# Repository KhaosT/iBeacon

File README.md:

iBeacon
=======
My own implementation of iBeacon.

/Eagle contains different version of hardware design. All designs based on TI CC2541.

/iOS contains a configurator for iBeacon used to setup UUID, Major and Minor when doing field work.

/Firmware contains firmware for CC2541.

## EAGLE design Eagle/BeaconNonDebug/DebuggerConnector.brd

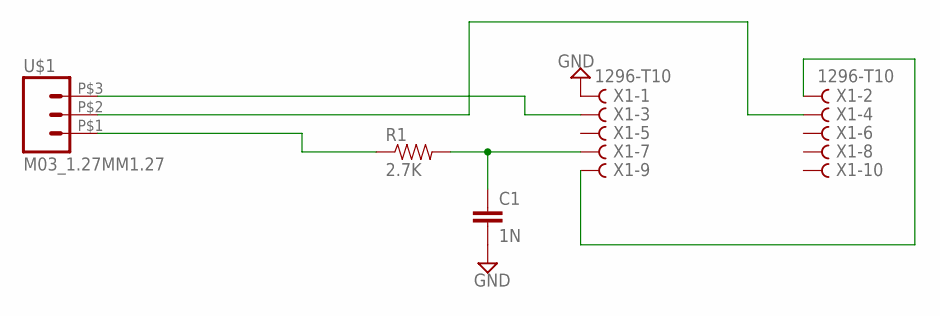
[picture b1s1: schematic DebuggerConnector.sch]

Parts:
C1: 1N; 0402-CAP
R1: 2.7K; 0402-RES
U$1: M03_1.27MM1.27; 1X3_1.27MM
X1: 1296-T10; 1296-10

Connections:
GND: C1.2, X1.1
unnamed: U$1.P$3 (3), X1.3
unnamed: U$1.P$2 (2), X1.4
unnamed: R1.1, U$1.P$1 (1)
unnamed: C1.1, R1.2, X1.7
unnamed: X1.2, X1.9

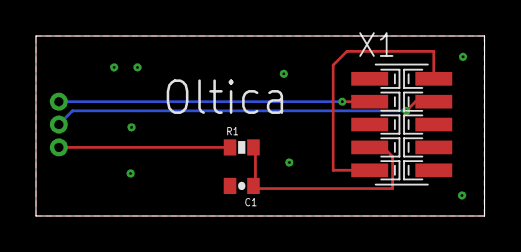
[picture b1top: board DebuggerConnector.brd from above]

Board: 2 copper layers, 24.9 x 10.0 mm, 4 parts (0 on the bottom side), 6 nets.

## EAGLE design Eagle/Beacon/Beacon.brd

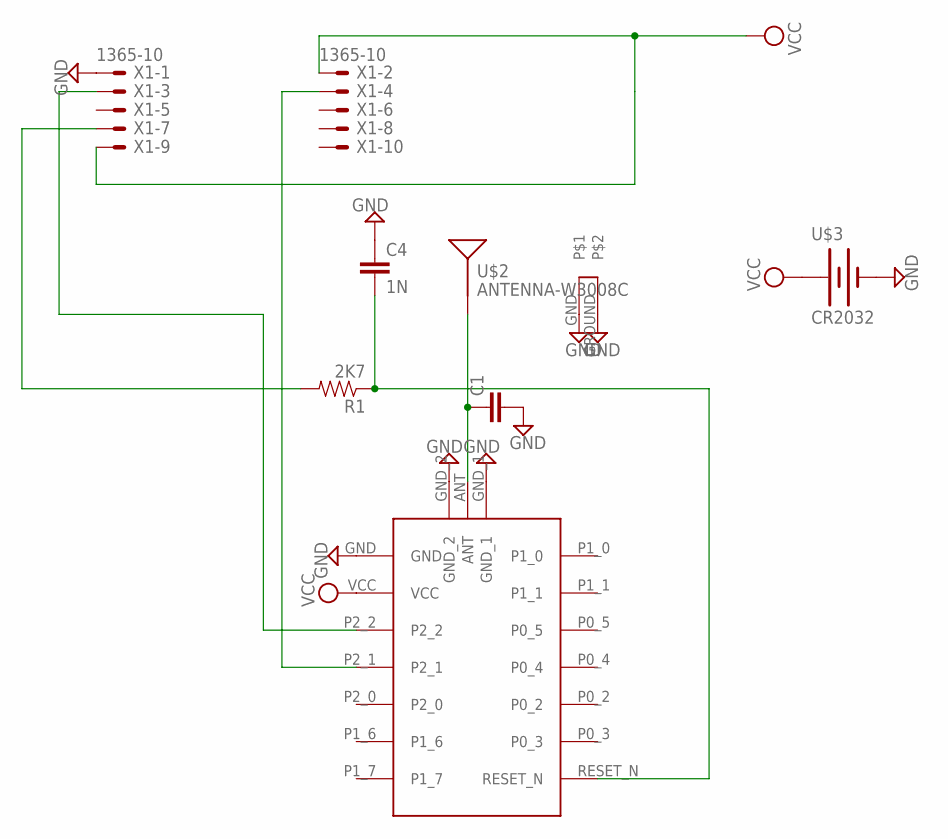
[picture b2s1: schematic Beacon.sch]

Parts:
C1: CAP0402-CAP; 0402-CAP
C4: 1N; 0402-CAP
R1: 2K7; 0402-RES
U$1: BLE4
U$2: ANTENNA-W3008C
U$3: CR2032; BATTCON_2032
X1: 1365-10

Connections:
GND: C1.2, C4.1, U$1.GND, U$1.GND_1, U$1.GND_2, U$2.GND, U$2.GROUND, U$3.PWR@2 (-), X1.1
unnamed: C1.1, U$1.ANT, U$2.FEED (SIGNAL)
unnamed: U$1.P2_2, X1.3
unnamed: C4.2, R1.1, U$1.RESET_N
unnamed: U$1.P2_1, X1.4
unnamed: R1.2, X1.7
VCC: U$1.VCC, U$3.PWR@1 (+), X1.2, X1.9

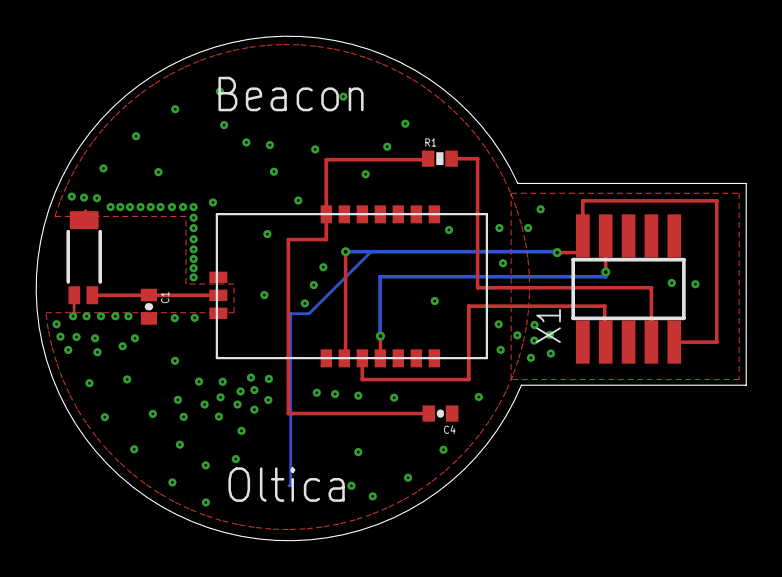
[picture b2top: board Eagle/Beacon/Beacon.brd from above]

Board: 2 copper layers, 39.4 x 28.0 mm, 7 parts (1 on the bottom side), 7 nets.

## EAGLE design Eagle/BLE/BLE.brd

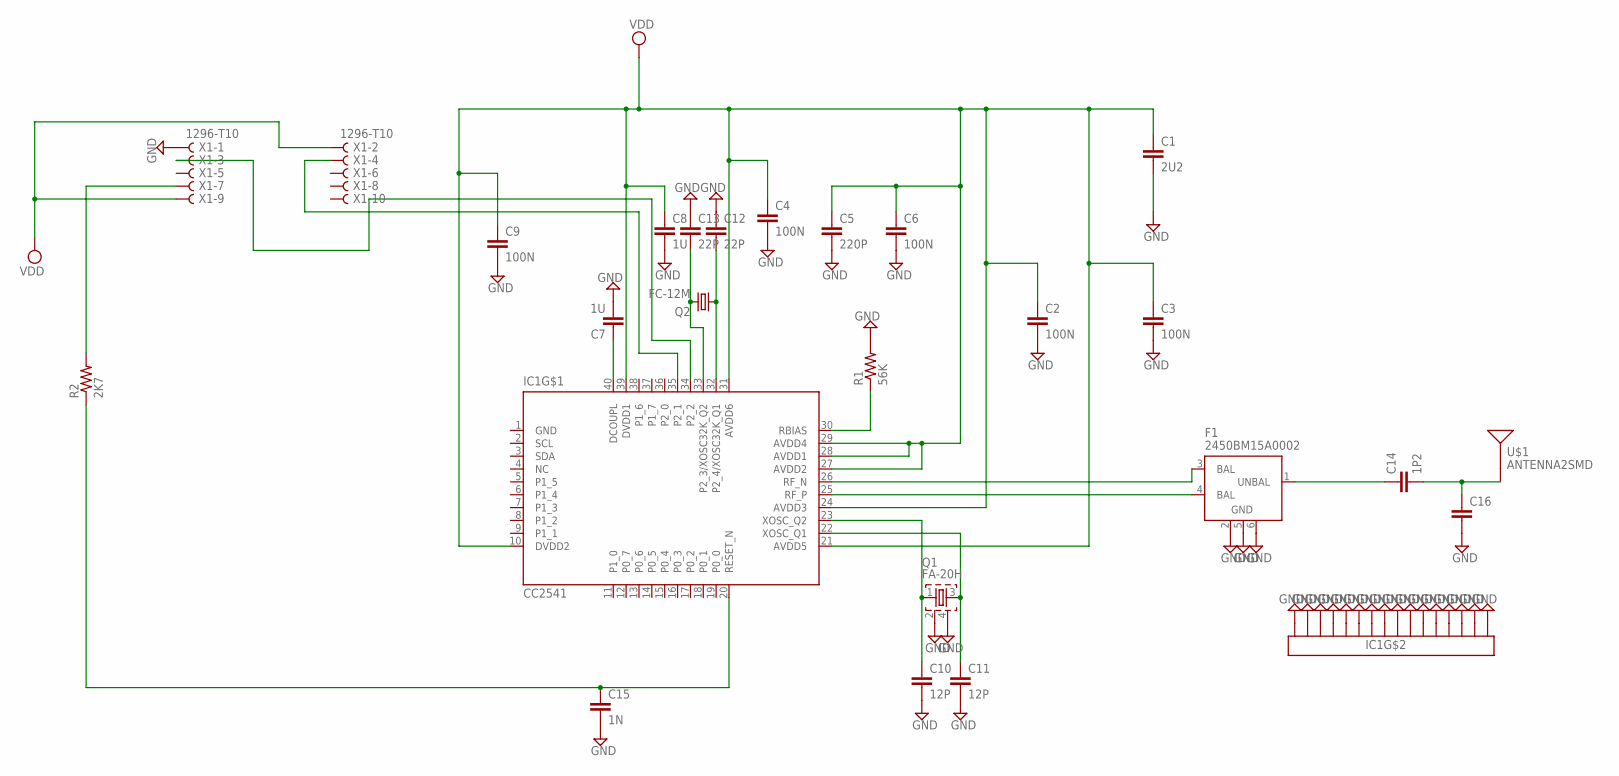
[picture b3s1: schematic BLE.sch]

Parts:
C1: 2U2; 0402-CAP
C2, C3, C4, C6, C9: 100N; 0402-CAP
C5: 220P; 0402-CAP
C7, C8: 1U; 0402-CAP
C10, C11: 12P; 0402-CAP
C12, C13: 22P; 0402-CAP
C14: 1P2; 0402-CAP
C15: 1N; 0402-CAP
C16: CAP0402-CAP; 0402-CAP
F1: 2450BM15A0002
IC1: CC2541; QFN40-6X6
Q1: FA-20H
Q2: FC-12M
R1: 56K; 0402-RES
R2: 2K7; 0402-RES
U$1: ANTENNA2SMD; ANTENNA-CHIP2
X1: 1296-T10; 1296-10

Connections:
GND: C1.2, C2.2, C3.2, C4.2, C5.2, C6.2, C7.2, C8.2, C9.2, C10.2, C11.2, C12.1, C13.1, C15.2, C16.2, F1.2 (GND), F1.5 (GND), F1.6 (GND), IC1.1 (GND), IC1.EXP@1 (EXP16), IC1.EXP@2 (EXP16), IC1.EXP@3 (EXP16), IC1.EXP@4 (EXP16), IC1.EXP@5 (EXP16), IC1.EXP@6 (EXP16), IC1.EXP@7 (EXP16), IC1.EXP@8 (EXP16), IC1.EXP@9 (EXP16), IC1.EXP@10 (EXP16), IC1.EXP@11 (EXP16), IC1.EXP@12 (EXP16), IC1.EXP@13 (EXP16), IC1.EXP@14 (EXP16), IC1.EXP@15 (EXP16), IC1.EXP@16 (EXP16), Q1.2, Q1.4, R1.2, X1.1
unnamed: IC1.30 (RBIAS), R1.1
unnamed: C7.1, IC1.40 (DCOUPL)
unnamed: C11.1, IC1.22 (XOSC_Q1), Q1.3
unnamed: C10.1, IC1.23 (XOSC_Q2), Q1.1
unnamed: C12.2, IC1.32 (P2_4/XOSC32K_Q1), Q2.1
unnamed: C13.2, IC1.33 (P2_3/XOSC32K_Q2), Q2.2
unnamed: F1.3 (BAL), IC1.26 (RF_N)
unnamed: F1.4 (BAL), IC1.25 (RF_P)
unnamed: C14.1, F1.1 (UNBAL)
unnamed: C14.2, C16.1, U$1.FEED
unnamed: C15.1, IC1.20 (RESET_N), R2.1
unnamed: R2.2, X1.7
unnamed: IC1.34 (P2_2), X1.3
unnamed: IC1.35 (P2_1), X1.4
NC: IC1.4 (NC)
VDD: C1.1, C2.1, C3.1, C4.1, C5.1, C6.1, C8.1, C9.1, IC1.10 (DVDD2), IC1.21 (AVDD5), IC1.24 (AVDD3), IC1.27 (AVDD2), IC1.28 (AVDD1), IC1.29 (AVDD4), IC1.31 (AVDD6), IC1.39 (DVDD1), X1.2, X1.9

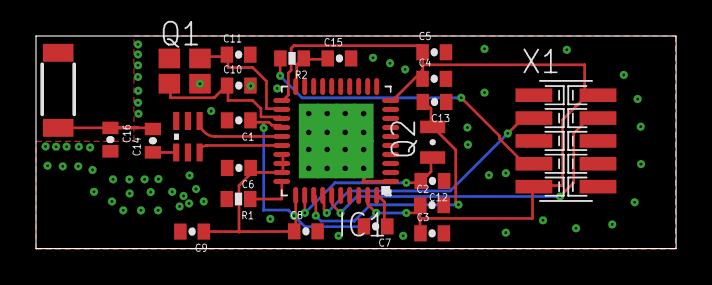
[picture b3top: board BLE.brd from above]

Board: 2 copper layers, 35.6 x 11.8 mm, 24 parts (0 on the bottom side), 16 nets.

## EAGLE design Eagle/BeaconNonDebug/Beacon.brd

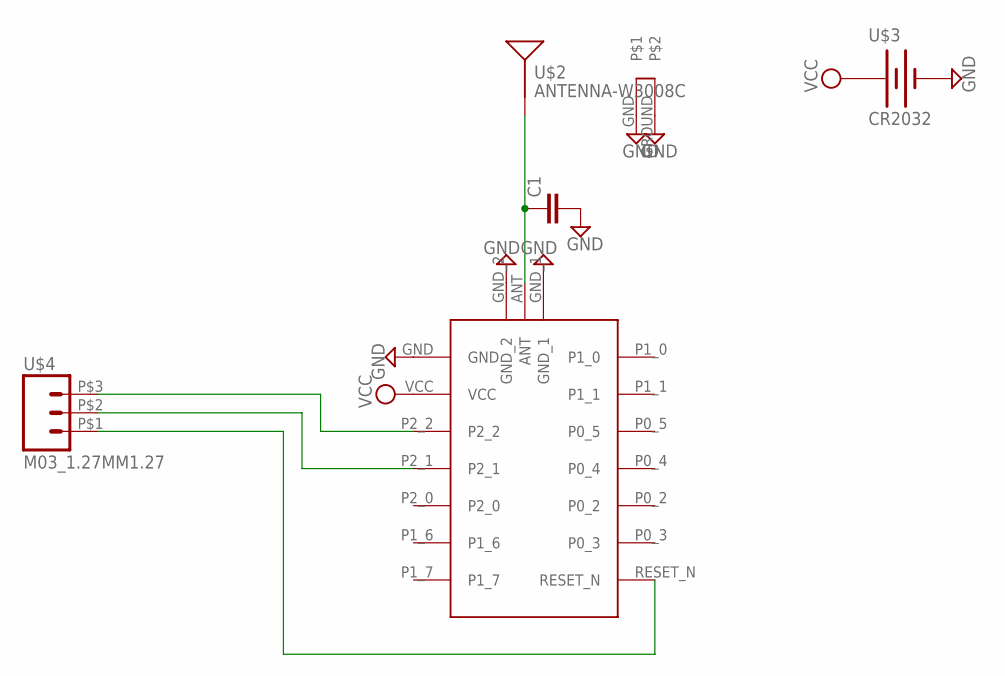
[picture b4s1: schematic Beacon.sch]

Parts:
C1: CAP0402-CAP; 0402-CAP
U$1: BLE4
U$2: ANTENNA-W3008C
U$3: CR2032; BATTCON_2032
U$4: M03_1.27MM1.27; 1X3_1.27MM

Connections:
GND: C1.2, U$1.GND, U$1.GND_1, U$1.GND_2, U$2.GND, U$2.GROUND, U$3.PWR@2 (-)
unnamed: C1.1, U$1.ANT, U$2.FEED (SIGNAL)
unnamed: U$1.P2_2, U$4.P$3 (3)
unnamed: U$1.P2_1, U$4.P$2 (2)
unnamed: U$1.RESET_N, U$4.P$1 (1)
VCC: U$1.VCC, U$3.PWR@1 (+)

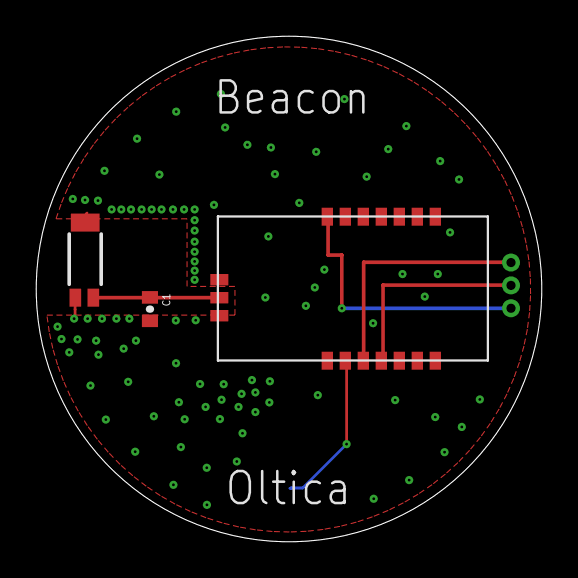
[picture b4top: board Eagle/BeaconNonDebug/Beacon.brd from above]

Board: 2 copper layers, 28.1 x 28.1 mm, 5 parts (1 on the bottom side), 6 nets.

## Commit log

2014-04-02 Init

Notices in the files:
parts and their libraries:
SparkFun-Capacitors: Licensing: CC v3.0 Share-Alike You are welcome to use this library for commercial purposes.
